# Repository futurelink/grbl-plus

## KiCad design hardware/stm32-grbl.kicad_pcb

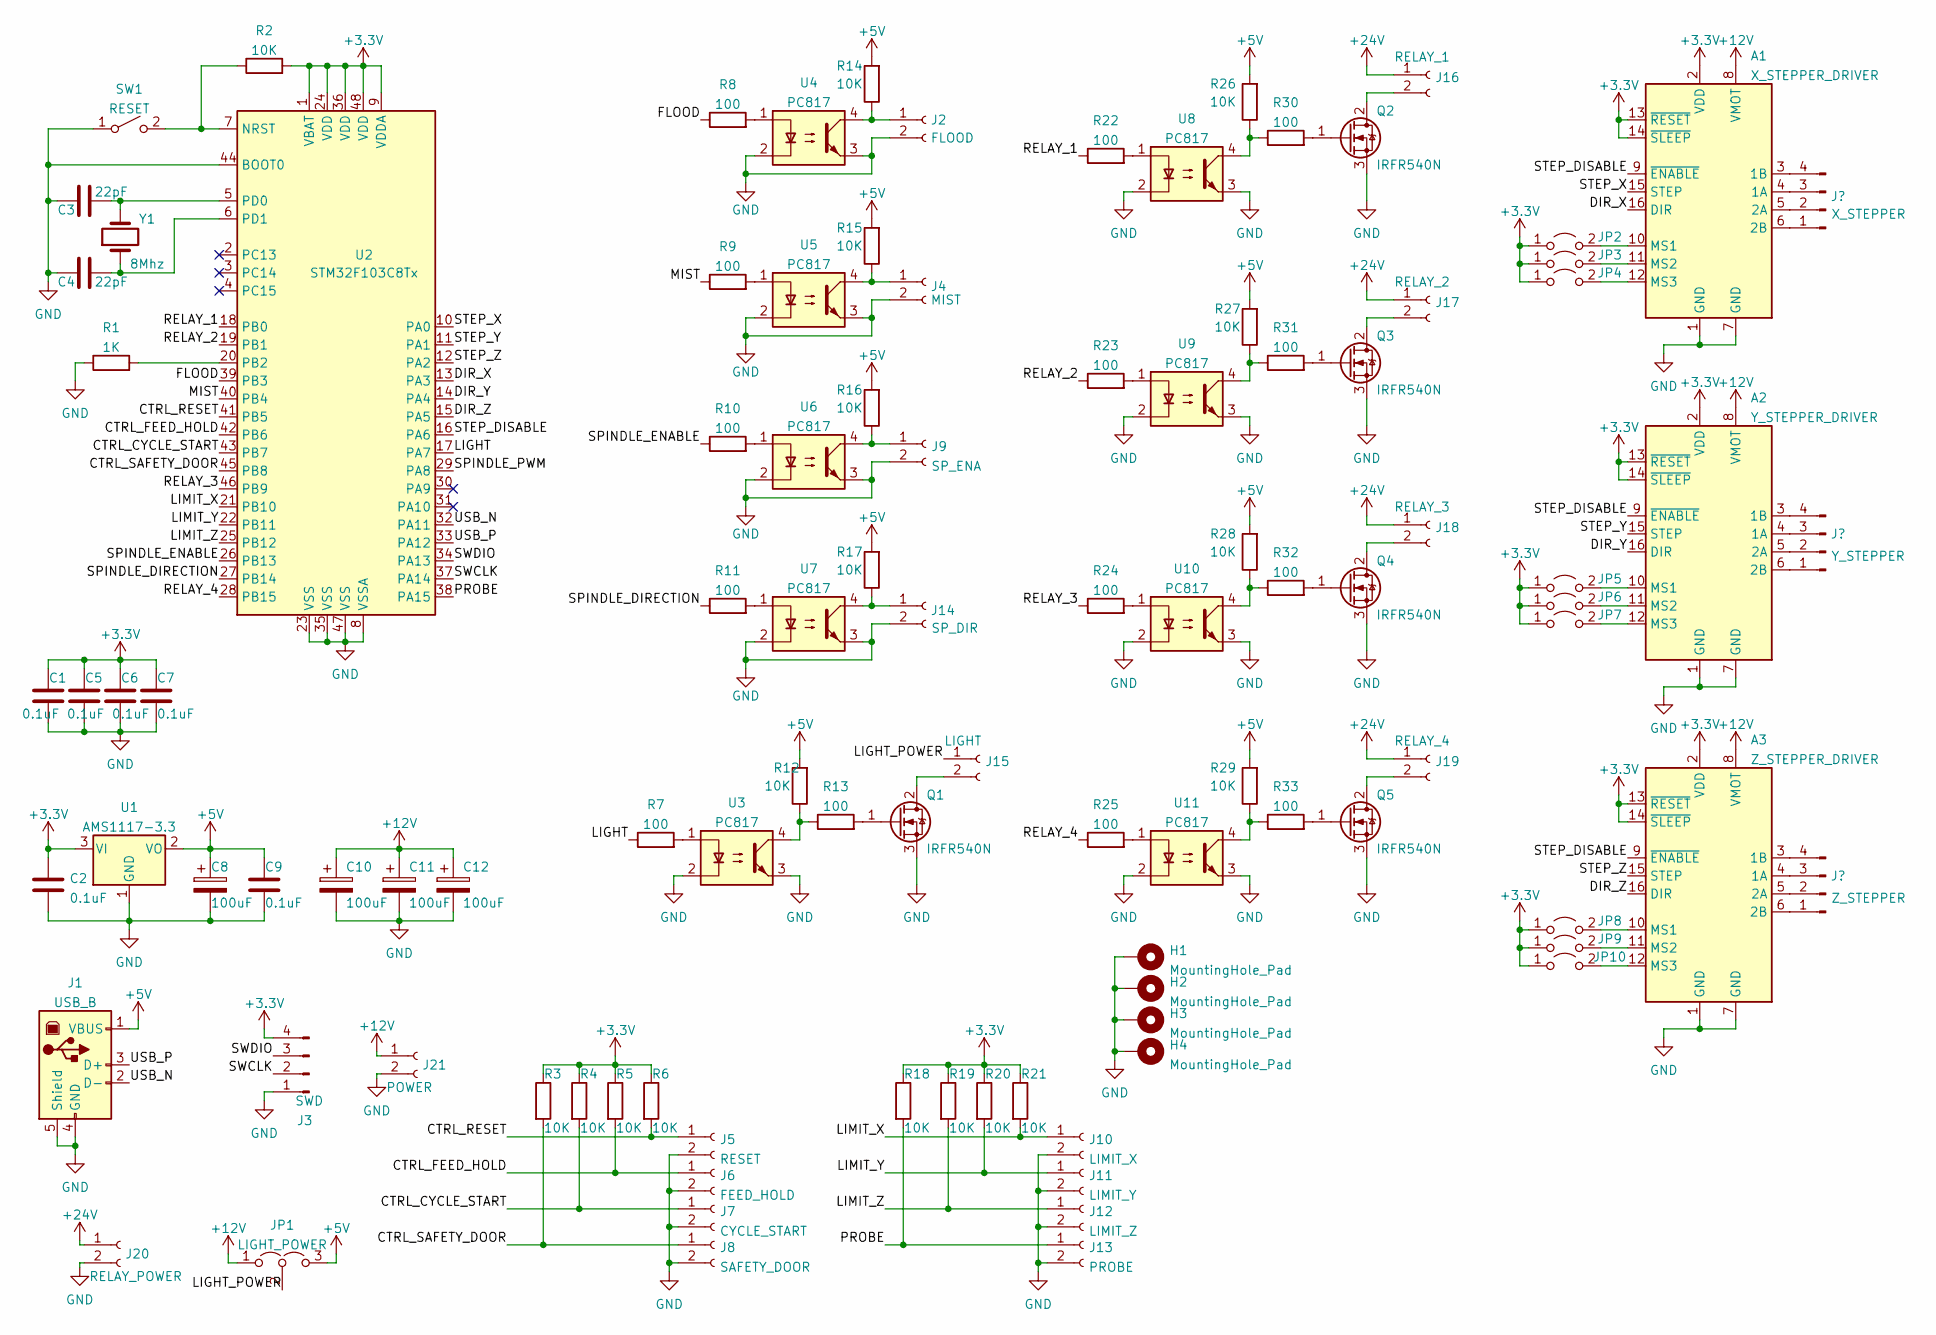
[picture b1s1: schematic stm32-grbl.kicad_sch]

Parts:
A1: X_STEPPER_DRIVER; Pololu_Breakout-16_15.2x20.3mm
A2: Y_STEPPER_DRIVER; Pololu_Breakout-16_15.2x20.3mm
A3: Z_STEPPER_DRIVER; Pololu_Breakout-16_15.2x20.3mm
C1, C2, C5, C6, C7, C9: 0.1uF; C_0805_2012Metric
C3, C4: 22pF; C_0805_2012Metric
C8: 100uF; CP_Elec_8x10
C10, C11, C12: 100uF; CP_Elec_6.3x7.7
H1, H2, H3, H4: MountingHole_Pad; MountingHole_3.2mm_M3_Pad
J1: USB_B; USB_B_OST_USB-B1HSxx_Horizontal
J2: FLOOD; JST_EH_B2B-EH-A_1x02_P2.50mm_Vertical
J3: SWD; PinHeader_1x04_P2.54mm_Vertical
J4: MIST; JST_EH_B2B-EH-A_1x02_P2.50mm_Vertical
J5: RESET; JST_EH_B2B-EH-A_1x02_P2.50mm_Vertical
J6: FEED_HOLD; JST_EH_B2B-EH-A_1x02_P2.50mm_Vertical
J7: CYCLE_START; JST_EH_B2B-EH-A_1x02_P2.50mm_Vertical
J8: SAFETY_DOOR; JST_EH_B2B-EH-A_1x02_P2.50mm_Vertical
J9: SP_ENA; JST_EH_B2B-EH-A_1x02_P2.50mm_Vertical
J10: LIMIT_X; JST_EH_B2B-EH-A_1x02_P2.50mm_Vertical
J11: LIMIT_Y; JST_EH_B2B-EH-A_1x02_P2.50mm_Vertical
J12: LIMIT_Z; JST_EH_B2B-EH-A_1x02_P2.50mm_Vertical
J13: PROBE; JST_EH_B2B-EH-A_1x02_P2.50mm_Vertical
J14: SP_DIR; JST_EH_B2B-EH-A_1x02_P2.50mm_Vertical
J15: LIGHT; JST_EH_B2B-EH-A_1x02_P2.50mm_Vertical
J16: RELAY_1; TerminalBlock_bornier-2_P5.08mm
J17: RELAY_2; TerminalBlock_bornier-2_P5.08mm
J18: RELAY_3; TerminalBlock_bornier-2_P5.08mm
J19: RELAY_4; TerminalBlock_bornier-2_P5.08mm
J20: RELAY_POWER; TerminalBlock_bornier-2_P5.08mm
J21: POWER; TerminalBlock_bornier-2_P5.08mm
JP1: LIGHT_POWER; PinHeader_1x03_P2.54mm_Vertical
JP2, JP3, JP4, JP5, JP6, JP7, JP8, JP9, JP10: Jumper_2_Open; PinHeader_1x02_P2.54mm_Vertical
Q1, Q2, Q3, Q4, Q5: IRFR540N; TO-252-2
R1: 1K; R_0805_2012Metric
R2, R3, R4, R5, R6, R12, R14, R15, R16, R17, R18, R19, R20, R21, R26, R27, R28, R29: 10K; R_0805_2012Metric
R7, R8, R9, R10, R11, R13, R22, R23, R24, R25, R30, R31, R32, R33: 100; R_0805_2012Metric
SW1: RESET; SW_Push_1P1T_NO_6x6mm_H9.5mm
U1: AMS1117-3.3; SOT-223-3_TabPin2
U2: STM32F103C8Tx; LQFP-48_7x7mm_P0.5mm
U3, U4, U5, U6, U7, U8, U9, U10, U11: PC817; SMDIP-4_W7.62mm
Y1: 8Mhz; Crystal_SMD_5032-2Pin_5.0x3.2mm

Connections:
+3V3: A1.2 (VDD), A1.13 (~RESET), A1.14 (~SLEEP), A2.2 (VDD), A2.13 (~RESET), A2.14 (~SLEEP), A3.2 (VDD), A3.13 (~RESET), A3.14 (~SLEEP), C1.1, C2.1, C5.1, C6.1, C7.1, J3.4, JP2.1 (A), JP3.1 (A), JP4.1 (A), JP5.1 (A), JP6.1 (A), JP7.1 (A), JP8.1 (A), JP9.1 (A), JP10.1 (A), R2.2, R3.1, R4.1, R5.1, R6.1, R18.1, R19.1, R20.1, R21.1, U1.3 (VI), U2.1 (VBAT), U2.9 (VDDA), U2.24 (VDD), U2.36 (VDD), U2.48 (VDD)
+5V: C8.1, C9.1, J1.1 (VBUS), JP1.3 (B), R12.2, R14.2, R15.2, R16.2, R17.2, R26.2, R27.2, R28.2, R29.2, U1.2 (VO)
+12V: A1.8 (VMOT), A2.8 (VMOT), A3.8 (VMOT), C10.1, C11.1, C12.1, J21.1, JP1.1 (A)
+24V: J16.1, J17.1, J18.1, J19.1, J20.1
/CTRL_CYCLE_START: J7.1, R4.2, U2.43 (PB7)
/CTRL_FEED_HOLD: J6.1, R5.2, U2.42 (PB6)
/CTRL_RESET: J5.1, R6.2, U2.41 (PB5)
/CTRL_SAFETY_DOOR: J8.1, R3.2, U2.45 (PB8)
/DIR_X: A1.16 (DIR), U2.13 (PA3)
/DIR_Y: A2.16 (DIR), U2.14 (PA4)
/DIR_Z: A3.16 (DIR), U2.15 (PA5)
/FLOOD: R8.1, U2.39 (PB3)
/LIGHT: R7.1, U2.17 (PA7)
/LIGHT_POWER: J15.1, JP1.2 (C)
/LIMIT_X: J10.1, R21.2, U2.21 (PB10)
/LIMIT_Y: J11.1, R20.2, U2.22 (PB11)
/LIMIT_Z: J12.1, R19.2, U2.25 (PB12)
/MIST: R9.1, U2.40 (PB4)
/PROBE: J13.1, R18.2, U2.38 (PA15)
/RELAY_1: R22.1, U2.18 (PB0)
/RELAY_2: R23.1, U2.19 (PB1)
/RELAY_3: R24.1, U2.46 (PB9)
/RELAY_4: R25.1, U2.28 (PB15)
/SPINDLE_DIRECTION: R11.1, U2.27 (PB14)
/SPINDLE_ENABLE: R10.1, U2.26 (PB13)
/SPINDLE_PWM: U2.29 (PA8)
/STEP_DISABLE: A1.9 (~ENABLE), A2.9 (~ENABLE), A3.9 (~ENABLE), U2.16 (PA6)
/STEP_X: A1.15 (STEP), U2.10 (PA0)
/STEP_Y: A2.15 (STEP), U2.11 (PA1)
/STEP_Z: A3.15 (STEP), U2.12 (PA2)
/SWCLK: J3.2, U2.37 (PA14)
/SWDIO: J3.3, U2.34 (PA13)
/USB_N: J1.2 (D-), U2.32 (PA11)
/USB_P: J1.3 (D+), U2.33 (PA12)
GND: A1.1 (GND), A1.7 (GND), A2.1 (GND), A2.7 (GND), A3.1 (GND), A3.7 (GND), C1.2, C2.2, C3.1, C4.1, C5.2, C6.2, C7.2, C8.2, C9.2, C10.2, C11.2, C12.2, H1.1, H2.1, H3.1, H4.1, J1.4 (GND), J1.5 (Shield), J2.2, J3.1, J4.2, J5.2, J6.2, J7.2, J8.2, J9.2, J10.2, J11.2, J12.2, J13.2, J14.2, J20.2, J21.2, Q1.3 (S), Q2.3 (S), Q3.3 (S), Q4.3 (S), Q5.3 (S), R1.1, SW1.1 (A), U1.1 (GND), U2.8 (VSSA), U2.23 (VSS), U2.35 (VSS), U2.44 (BOOT0), U2.47 (VSS), U3.2, U3.3, U4.2, U4.3, U5.2, U5.3, U6.2, U6.3, U7.2, U7.3, U8.2, U8.3, U9.2, U9.3, U10.2, U10.3, U11.2, U11.3
unnamed 35: A1.3 (1B); also elsewhere on the board
unnamed 36: A1.4 (1A); also elsewhere on the board
unnamed 37: A1.5 (2A); also elsewhere on the board
unnamed 38: A1.6 (2B); also elsewhere on the board
unnamed: A1.10 (MS1), JP2.2 (B)
unnamed: A1.11 (MS2), JP3.2 (B)
unnamed: A1.12 (MS3), JP4.2 (B)
unnamed 42: A2.3 (1B); also elsewhere on the board
unnamed 43: A2.4 (1A); also elsewhere on the board
unnamed 44: A2.5 (2A); also elsewhere on the board
unnamed 45: A2.6 (2B); also elsewhere on the board
unnamed: A2.10 (MS1), JP5.2 (B)
unnamed: A2.11 (MS2), JP6.2 (B)
unnamed: A2.12 (MS3), JP7.2 (B)
unnamed 49: A3.3 (1B); also elsewhere on the board
unnamed 50: A3.4 (1A); also elsewhere on the board
unnamed 51: A3.5 (2A); also elsewhere on the board
unnamed 52: A3.6 (2B); also elsewhere on the board
unnamed: A3.10 (MS1), JP8.2 (B)
unnamed: A3.11 (MS2), JP9.2 (B)
unnamed: A3.12 (MS3), JP10.2 (B)
unnamed: C3.2, U2.5 (PD0), Y1.2
unnamed: C4.2, U2.6 (PD1), Y1.1
unnamed: Q1.1 (G), R13.2
unnamed: J15.2, Q1.2 (D)
unnamed: Q2.1 (G), R30.2
unnamed: J16.2, Q2.2 (D)
unnamed: Q3.1 (G), R31.2
unnamed: J17.2, Q3.2 (D)
unnamed: Q4.1 (G), R32.2
unnamed: J18.2, Q4.2 (D)
unnamed: Q5.1 (G), R33.2
unnamed: J19.2, Q5.2 (D)
unnamed: R1.2, U2.20 (PB2)
unnamed: R2.1, SW1.2 (B), U2.7 (NRST)
unnamed: R7.2, U3.1
unnamed: R8.2, U4.1
unnamed: R9.2, U5.1
unnamed: R10.2, U6.1
unnamed: R11.2, U7.1
unnamed: R12.1, R13.1, U3.4
unnamed: J2.1, R14.1, U4.4
unnamed: J4.1, R15.1, U5.4
unnamed: J9.1, R16.1, U6.4
unnamed: J14.1, R17.1, U7.4
unnamed: R22.2, U8.1
unnamed: R23.2, U9.1
unnamed: R24.2, U10.1
unnamed: R25.2, U11.1
unnamed: R26.1, R30.1, U8.4
unnamed: R27.1, R31.1, U9.4
unnamed: R28.1, R32.1, U10.4
unnamed: R29.1, R33.1, U11.4

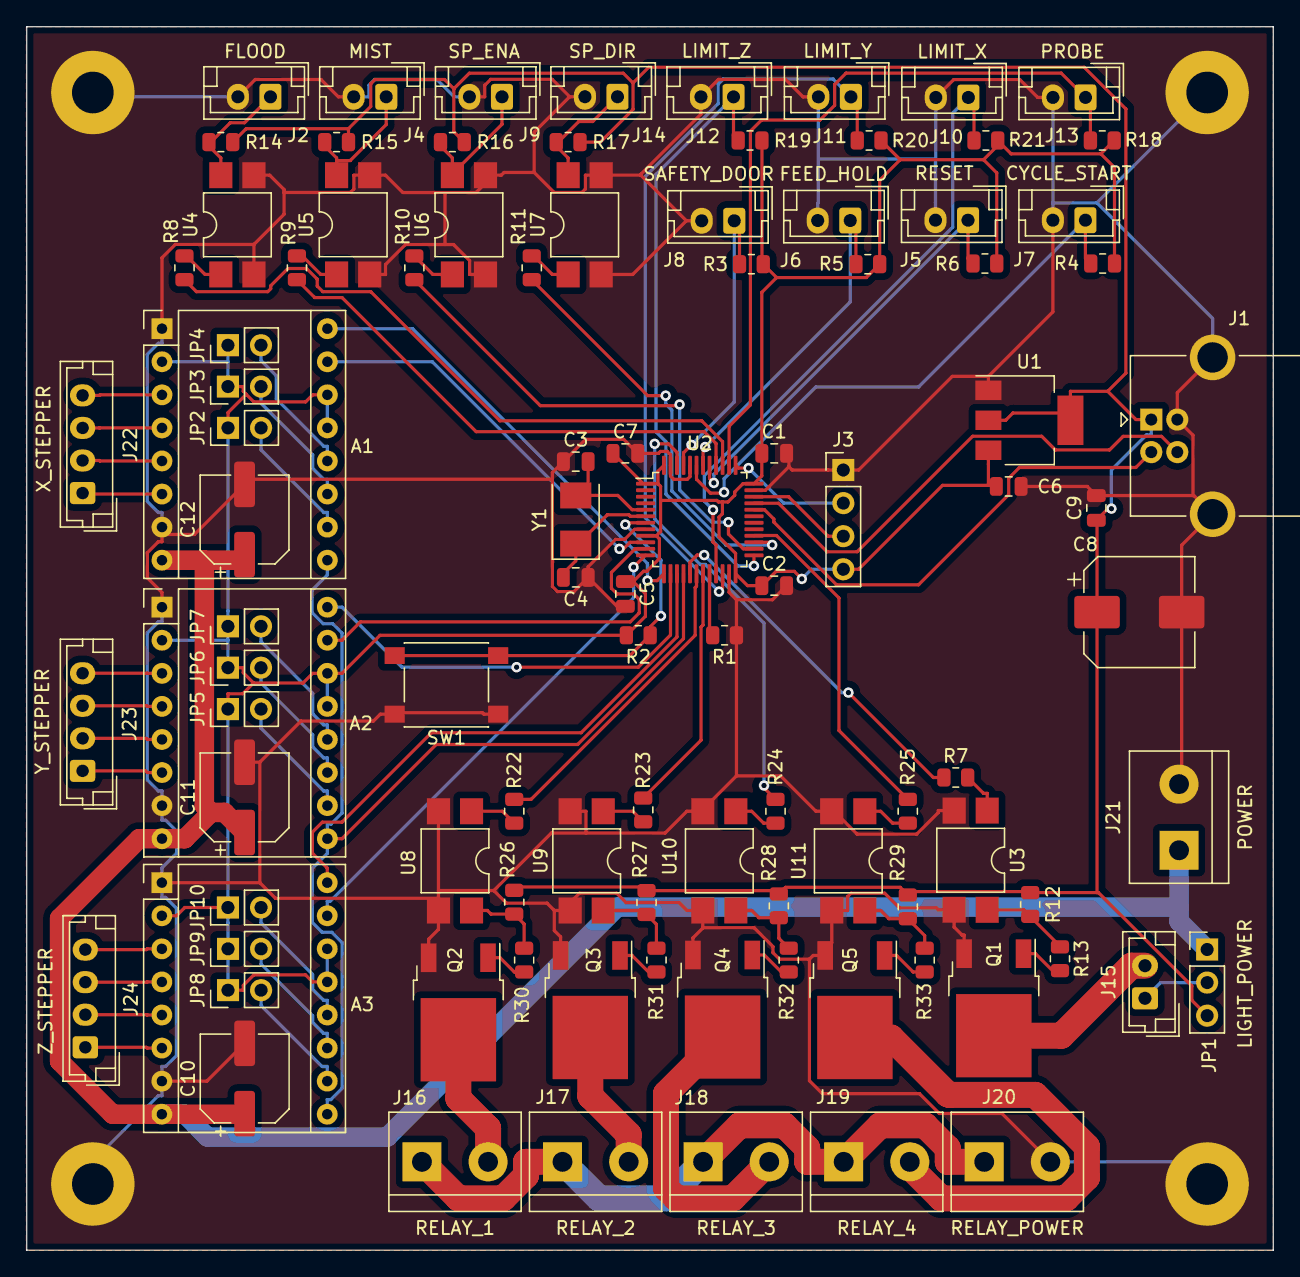
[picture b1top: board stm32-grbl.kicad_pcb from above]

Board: 2 copper layers, 95.7 x 94.0 mm, 104 parts (0 on the bottom side), 87 nets.

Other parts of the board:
J22: X_STEPPER; JST_EH_B4B-EH-A_1x04_P2.50mm_Vertical
J23: Y_STEPPER; JST_EH_B4B-EH-A_1x04_P2.50mm_Vertical
J24: Z_STEPPER; JST_EH_B4B-EH-A_1x04_P2.50mm_Vertical

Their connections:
unnamed 35: J22.4; also elsewhere on the board
unnamed 36: J22.3; also elsewhere on the board
unnamed 37: J22.2; also elsewhere on the board
unnamed 38: J22.1; also elsewhere on the board
unnamed 42: J23.4; also elsewhere on the board
unnamed 43: J23.3; also elsewhere on the board
unnamed 44: J23.2; also elsewhere on the board
unnamed 45: J23.1; also elsewhere on the board
unnamed 49: J24.4; also elsewhere on the board
unnamed 50: J24.3; also elsewhere on the board
unnamed 51: J24.2; also elsewhere on the board
unnamed 52: J24.1; also elsewhere on the board

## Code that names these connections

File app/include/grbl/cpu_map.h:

/*
  cpu_map.h - CPU and pin mapping configuration file
  Part of Grbl

  Copyright (c) 2012-2016 Sungeun K. Jeon for Gnea Research LLC
  Copyright (c) 2022 Denis Pavlov

  Grbl is free software: you can redistribute it and/or modify
  it under the terms of the GNU General Public License as published by
  the Free Software Foundation, either version 3 of the License, or
  (at your option) any later version.

  Grbl is distributed in the hope that it will be useful,
  but WITHOUT ANY WARRANTY; without even the implied warranty of
  MERCHANTABILITY or FITNESS FOR A PARTICULAR PURPOSE.  See the
  GNU General Public License for more details.

  You should have received a copy of the GNU General Public License
  along with Grbl.  If not, see <http://www.gnu.org/licenses/>.
*/

/* The cpu_map.h files serve as a central pin mapping selection file for different
   processor types or alternative pin layouts. This version of Grbl officially supports
   only the Arduino Mega328p. */


#ifndef cpu_map_h
#define cpu_map_h

#ifdef CPU_MAP_STM32F103

  // Define step pulse output pins. NOTE: All step bit pins must be on the same port.
#define STEP_PORT           GPIOA
#define X_STEP_BIT          0
#define Y_STEP_BIT          1
#define Z_STEP_BIT          2
#define STEP_MASK           ((1<<X_STEP_BIT)|(1<<Y_STEP_BIT)|(1<<Z_STEP_BIT)) // All step bits

  // Define step direction output pins. NOTE: All direction pins must be on the same port.
#define DIRECTION_PORT      GPIOA
#define X_DIRECTION_BIT     3
#define Y_DIRECTION_BIT     4
#define Z_DIRECTION_BIT     5
#define DIRECTION_MASK      ((1<<X_DIRECTION_BIT)|(1<<Y_DIRECTION_BIT)|(1<<Z_DIRECTION_BIT)) // All direction bits

  // Define stepper driver enable/disable output pin.
#define STEPPERS_DISABLE_PORT       GPIOA
#define STEPPERS_DISABLE_BIT        6
#define STEPPERS_DISABLE_MASK       (1<<STEPPERS_DISABLE_BIT)
#define SetStepperDisableBit()      HAL_GPIO_WritePin(STEPPERS_DISABLE_PORT,STEPPERS_DISABLE_MASK,GPIO_PIN_SET)
#define ResetStepperDisableBit()    HAL_GPIO_WritePin(STEPPERS_DISABLE_PORT,STEPPERS_DISABLE_MASK,GPIO_PIN_RESET)

  // Define homing/hard limit switch input pins and limit interrupt vectors. 
  // NOTE: All limit bit pins must be on the same port
#define LIMIT_PORT       GPIOB
#define X_LIMIT_BIT      10
#define Y_LIMIT_BIT      11  
#define Z_LIMIT_BIT      12
#define LIMIT_MASK       ((1 << X_LIMIT_BIT) | (1 << Y_LIMIT_BIT) | (1 << Z_LIMIT_BIT)) // All limit bits

  // Define spindle enable and spindle direction output pins.
#define SPINDLE_ENABLE_PORT   GPIOB
#define SPINDLE_ENABLE_BIT    13  //
#ifndef USE_SPINDLE_DIR_AS_ENABLE_PIN
#define SPINDLE_DIRECTION_PORT  GPIOB
#define SPINDLE_DIRECTION_BIT   14  // 
#endif
#define SetSpindleEnableBit()       HAL_GPIO_WritePin(SPINDLE_ENABLE_PORT, SPINDLE_ENABLE_BIT, GPIO_PIN_SET)
#define ResetSpindleEnableBit()     HAL_GPIO_WritePin(SPINDLE_ENABLE_PORT, SPINDLE_ENABLE_BIT, GPIO_PIN_RESET)
#define SetSpindleDirectionBit()    HAL_GPIO_WritePin(SPINDLE_DIRECTION_PORT, SPINDLE_DIRECTION_BIT, GPIO_PIN_SET)
#define ResetSpindleDirectionBit()  HAL_GPIO_WritePin(SPINDLE_DIRECTION_PORT, SPINDLE_DIRECTION_BIT, GPIO_PIN_RESET)


  // Define flood and mist coolant enable output pins.
  // a later date if flash and memory space allows.
#define COOLANT_FLOOD_PORT            GPIOB
#define COOLANT_FLOOD_BIT             3
#define COOLANT_MIST_PORT             GPIOB
#define COOLANT_MIST_BIT              4

  // Define user-control controls (cycle start, reset, feed hold) input pins.
  // NOTE: All CONTROLs pins must be on the same port and not on a port with other input pins (limits).
#define CONTROL_PIN_PORT              GPIOB
#define CONTROL_PORT                  GPIOB
#define CONTROL_RESET_BIT             5
#define CONTROL_FEED_HOLD_BIT         6  
#define CONTROL_CYCLE_START_BIT       7  
#define CONTROL_SAFETY_DOOR_BIT       8  
#define CONTROL_MASK                 ((1<<CONTROL_RESET_BIT)|(1<<CONTROL_FEED_HOLD_BIT)|(1<<CONTROL_CYCLE_START_BIT)|(1<<CONTROL_SAFETY_DOOR_BIT))

  // Define probe switch input pin.
#define PROBE_PORT                    GPIOA
#define PROBE_BIT                     15
#define PROBE_MASK                    (1<<PROBE_BIT)

  // Start of PWM & Stepper Enabled Spindle
#ifdef VARIABLE_SPINDLE

  // NOTE: On the 328p, these must be the same as the SPINDLE_ENABLE settings.
#define SPINDLE_PWM_FREQUENCY       10000                   // KHz
#define SPINDLE_PWM_PORT            GPIOA
#define SPINDLE_PWM_BIT	            8    
#endif // End of VARIABLE_SPINDLE
#define SPINDLE_PWM_MAX_VALUE       (1000000 / SPINDLE_PWM_FREQUENCY)
#ifndef SPINDLE_PWM_MIN_VALUE
#define SPINDLE_PWM_MIN_VALUE       1   // Must be greater than zero.
#endif
#define SPINDLE_PWM_OFF_VALUE       0
#define SPINDLE_PWM_RANGE           (SPINDLE_PWM_MAX_VALUE-SPINDLE_PWM_MIN_VALUE)

  //  Port A                                         Port B
  //   0      X_STEP_BIT                             
  //   1      Y_STEP_BIT                            
  //   2      Z_STEP_BIT                               
  //   3      X_DIRECTION_BIT                       COOLANT_FLOOD_BIT
  //   4      Y_DIRECTION_BIT                       COOLANT_MIST_BIT
  //   5      Z_DIRECTION_BIT                       CONTROL_RESET_BIT
  //   6      STEPPERS_DISABLE_BIT                  CONTROL_FEED_HOLD_BIT    
  //   7                                            CONTROL_CYCLE_START_BIT
  //   8      SPINDLE_PWM_BIT                       CONTROL_SAFETY_DOOR_BIT    
  //   9                             
  //   10                                           X_LIMIT_BIT
  //   11                                           Y_LIMIT_BIT
  //   12                                           Z_LIMIT_BIT
  //   13     SWD									SPINDLE_ENABLE_BIT
  //   14	  SWD   								SPINDLE_DIRECTION_BIT
  //   15     PROBE_BIT					

#endif

/*
#ifdef CPU_MAP_CUSTOM_PROC
  // For a custom pin map or different processor, copy and edit one of the available cpu
  // map files and modify it to your needs. Make sure the defined name is also changed in
  // the config.h file.
#endif
*/

#endif

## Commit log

2022-02-20 Migration to C++ compiler
2022-02-20 Partially made classes
2022-02-20 Spindle made as class
2022-02-20 Motion made as a class
2022-02-20 Probe made as a class
2022-02-20 Coolant made as a class
2022-02-20 GCode made as a class
2022-02-20 Limits made as a class
2022-02-20 System made as a class
2022-02-20 Reports made as a class
2022-02-20 FAIL warn fix
2022-02-20 Serial made as a class
2022-02-20 Protocol made as a class
2022-02-21 Some tidy up
2022-02-21 Some work with steppers.
2022-02-21 moved headers
2022-02-21 Moved system props to GRBLSystem class
2022-02-21 Safety door improvements
2022-02-21 Rest of system props moved to GRBLSystem
2022-02-21 Removed printPgmString
2022-02-22 Hardware implementation
2022-02-22 HW update
